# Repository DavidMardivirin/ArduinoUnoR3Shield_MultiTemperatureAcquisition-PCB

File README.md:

## Arduino UNO R3 Schield for Multiple Temperatures Acquisition

PCB files. Format is KiCad (7.0) shcematic and layout

### Description
The Schield is connected on the Arduino UNO footprint.
The design is made for adding to the UNO bord 6 modules
- 1 DS3231 based Realtime Clock (RTC)  to manage time and data saving on the acquisitions
- 1 DHT11 environmental sensor module (Temperature and humidity)
- 5 MAX31856 thermocouple type  converter modules

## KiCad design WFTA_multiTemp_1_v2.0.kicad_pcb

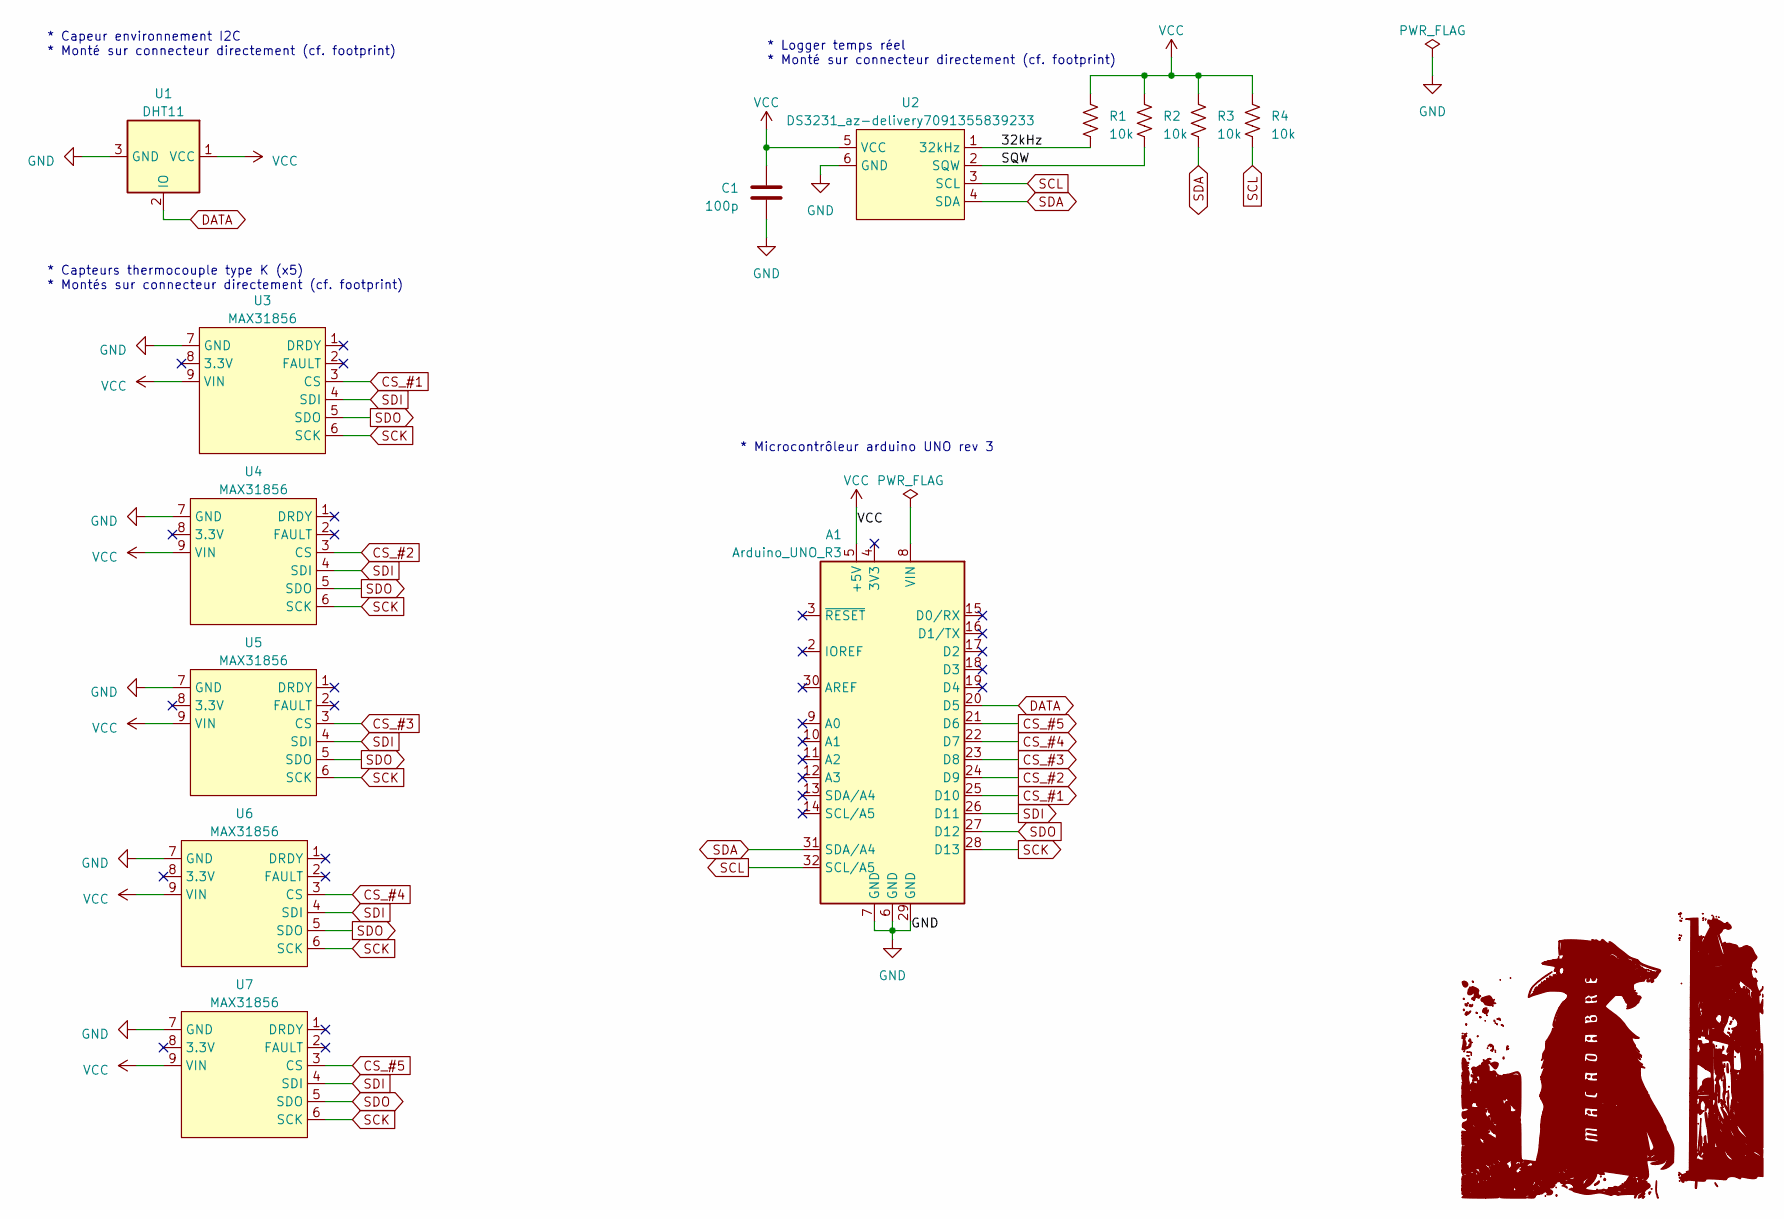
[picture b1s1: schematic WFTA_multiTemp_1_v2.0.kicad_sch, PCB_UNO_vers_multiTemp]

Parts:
A1: Arduino_UNO_R3; Arduino_UNO_R3_SchieldInterface
C1: 100p; C_0805_2012Metric_Pad1.18x1.45mm_HandSolder
R1, R2, R3, R4: 10k; R_0805_2012Metric_Pad1.20x1.40mm_HandSolder
U1: DHT11; PinSocket_1x03_P2.54mm_Vertical
U2: DS3231_az-delivery7091355839233; PinSocket_1x06_P2.54mm_Vertical
U3, U4, U5, U6, U7: MAX31856; PinSocket_1x09_P2.54mm_Vertical

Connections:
/32kHz: R1.2, U2.1 (32kHz)
/SQW: R2.2, U2.2 (SQW)
CS_#1: A1.25 (D10), U3.3 (CS)
CS_#2: A1.24 (D9), U4.3 (CS)
CS_#3: A1.23 (D8), U5.3 (CS)
CS_#4: A1.22 (D7), U6.3 (CS)
CS_#5: A1.21 (D6), U7.3 (CS)
DATA: A1.20 (D5), U1.2 (IO)
GND: A1.6 (GND), A1.7 (GND), A1.29 (GND), C1.2, U1.3 (GND), U2.6 (GND), U3.7 (GND), U4.7 (GND), U5.7 (GND), U6.7 (GND), U7.7 (GND)
SCK: A1.28 (D13), U3.6 (SCK), U4.6 (SCK), U5.6 (SCK), U6.6 (SCK), U7.6 (SCK)
SCL: A1.32 (SCL/A5), R4.2, U2.3 (SCL)
SDA: A1.31 (SDA/A4), R3.2, U2.4 (SDA)
SDI: A1.26 (D11), U3.4 (SDI), U4.4 (SDI), U5.4 (SDI), U6.4 (SDI), U7.4 (SDI)
SDO: A1.27 (D12), U3.5 (SDO), U4.5 (SDO), U5.5 (SDO), U6.5 (SDO), U7.5 (SDO)
VCC: A1.5 (+5V), C1.1, R1.1, R2.1, R3.1, R4.1, U1.1 (VCC), U2.5 (VCC), U3.9 (VIN), U4.9 (VIN), U5.9 (VIN), U6.9 (VIN), U7.9 (VIN)

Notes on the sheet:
* Logger temps réel * Monté sur connecteur directement (cf. footprint)
* Microcontrôleur arduino UNO rev 3
* Capteurs thermocouple type K (x5) * Montés sur connecteur directement (cf. footprint)
* Capeur environnement I2C * Monté sur connecteur directement (cf. footprint)

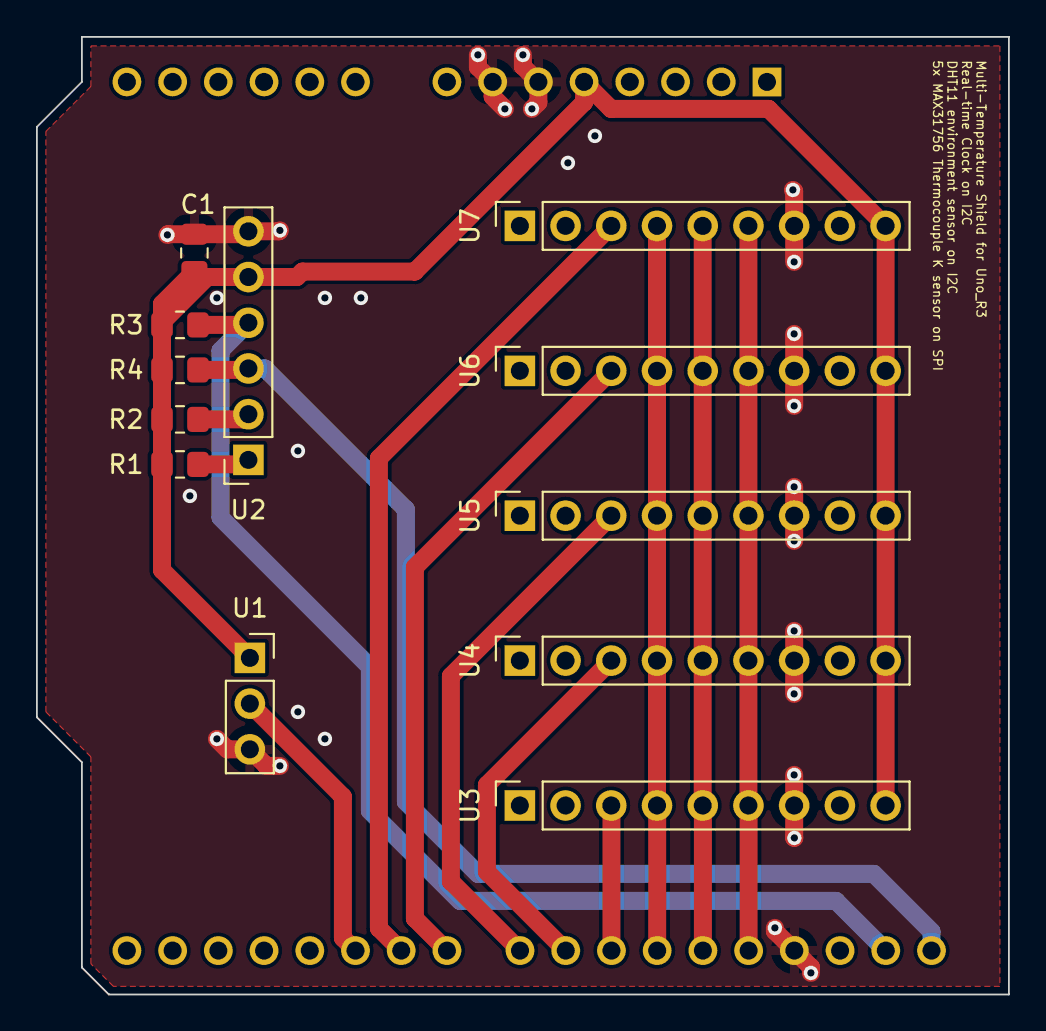
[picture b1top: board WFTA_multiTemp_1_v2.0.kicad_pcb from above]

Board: 2 copper layers, 54.0 x 53.2 mm, 13 parts (1 on the bottom side), 15 nets.
